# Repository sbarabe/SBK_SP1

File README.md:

# SBK_SP1

<p align="center">
  
  &nbsp;&nbsp;&nbsp;
  
</p>

<p align="center">
  <b>Front</b> &nbsp;&nbsp;&nbsp;&nbsp;&nbsp;&nbsp;&nbsp;&nbsp;&nbsp;&nbsp;&nbsp;&nbsp;&nbsp;&nbsp;&nbsp;&nbsp;&nbsp;&nbsp;&nbsp;&nbsp;&nbsp;&nbsp;&nbsp;&nbsp;&nbsp;&nbsp;&nbsp;
  <b>Back</b>
</p>

---

## Open-source soft power switch module for learning and embedded electronics projects.

**SBK_SP1** is a compact, reusable soft power switch module for battery-powered and low-voltage embedded systems. 

A momentary push button, maintained switch, or external control can turn the system on. Once powered, a microcontroller can assert the **HOLD** input to keep the system running independently of the switch state. 

**Version 2.0** adds an onboard start button, a dedicated external **SW** input, and an independent **SENS** output. This allows the microcontroller to continue monitoring the external switch while holding its own power on, making graceful software-controlled shutdown possible. 

Designed for breadboards, prototypes, and educational projects, **SBK_SP1** provides an easy way to add soft power management to Arduino, ESP32, RP2040, ATtiny, STM32, and similar microcontroller-based systems.

---

## Features

- Input voltage: **2–12 VDC**
- Load current: **up to 2 A**
- High-side **P-channel MOSFET** switching
- MCU-controlled soft power latch
- Onboard power/start button
- External momentary button or maintained switch input
- Independent switch-state sensing
- Supports graceful MCU-controlled shutdown
- Ultra-low off-state current (< 1 µA typ.)
- Power input and output status LEDs
- Breadboard-friendly 2.54 mm pin header
- Open-source hardware
- Optimized for low-cost assembly using JLCPCB Basic components

---

## Specifications 
| Parameter | Specification | 
|---|---| 
| Input voltage | 2–12 VDC | 
| Maximum load | 2 A | 
| Off-state current | < 1 µA typical | 
| HOLD input | Active HIGH, 2 V–VIN | 
| SW input | Active LOW, connect to GND | 
| SENS output | Active LOW, external/MCU pull-up required | 
| PCB size | 15.8 × 11.2 mm | | Pin pitch | 2.54 mm |

---

## Pinout

| Pin | Description |
|------|-------------|
| **VIN** | Power input (2–12 VDC) |
| **GND** | Ground |
| **VOUT** | Switched power output |
| **HOLD** | Active-HIGH MCU power-hold input. Drive HIGH (2 V–VIN) to keep VOUT enabled. | 
| **SW** | Active-LOW external switch input. Connect to GND to start/activate the module. | 
| **SENS** | Active-LOW switch-sense output. Connect to an MCU input with an internal or external pull-up. | 

The onboard push button is connected to the **SW** and **SENS** functions and can be used to start the module without an external switch.

---

## Typical Application

```text
Battery / Power Supply
         │
         │
        VIN
   ┌───────────┐
   │  SBK_SP1  │
   │           │
   │   VOUT    ├──────────> Embedded System Power
   │           │
MCU├─ HOLD <───┤ MCU output
   │           │
MCU├─ SENS ───>│ MCU input with pull-up
   │           │
   │    SW     ├──── Switch / Push Button ──── GND
   └───────────┘
         │
        GND
```

---

## Operation

### Power On
1. The user presses the onboard button or connects **SW** to GND.
2. The hardware immediately enables the high-side power MOSFET.
3. **VOUT** powers the microcontroller and load.
4. **SENS** goes **LOW**, allowing the microcontroller to detect the active switch.
5. The microcontroller boots and drives **HOLD HIGH**.
6. The module remains powered after a momentary button is released.

### Power Hold

While **HOLD** is **HIGH**, the microcontroller keeps **VOUT** enabled independently of the state of **SW**.

Because **SENS** monitors the switch separately from the **HOLD** circuit, the microcontroller can continue detecting button presses, button releases, or changes in a maintained external switch while power remains latched.

### Graceful Shutdown

With a maintained ON/OFF switch, SBK_SP1 can support a software-controlled shutdown sequence:

1. The external switch connects **SW** to **GND** to start the system.
2. The microcontroller boots and drives **HOLD HIGH**.
3. The user opens the external switch.
4. **SENS** returns **HIGH** while **HOLD** keeps the system powered.
5. The microcontroller detects the switch change and performs any required shutdown tasks.
6. When shutdown is complete, the microcontroller drives **HOLD LOW**.
7. **SBK_SP1** disconnects **VOUT** from the load.

This allows firmware to save data, stop peripherals, or perform other cleanup before removing power.

---

## Using a Momentary Push Button

SBK_SP1 can also be used with a conventional momentary push button.

Connect the external button between **SW** and **GND**, or simply use the onboard button.

A button press starts the system and pulls **SENS LOW**. The microcontroller can then assert **HOLD** to keep itself powered after the button is released.

Because **SENS** remains independent of **HOLD**, the same button can continue to be monitored by the firmware while the system is running.

---

## Applications

### Microcontroller platforms

- Arduino
- ESP32
- RP2040
- ATtiny
- STM32

### Example applications

- Portable instruments
- Battery-powered sensors
- Educational electronics projects
- Custom embedded devices
  
---

## Notes

- **HOLD** is an active-HIGH input and should not exceed **VIN**.
- **SW** is an active-LOW input and is activated by connecting it to **GND**.
- **SENS** is an active-LOW sense signal and requires an external or MCU internal pull-up.
- The onboard push button and external **SW** input operate in parallel.
- Do not apply an external positive voltage directly to **SW**.
- Inductive loads require an external flyback diode or equivalent protection.
- High-capacitance loads may require inrush-current limiting.
- The 2 A rating is the maximum recommended module load; consider wiring, connector, thermal, and application conditions when operating near the maximum current.

---

## Getting Started

This project is fully open-source hardware. You can:

- Build your own module using the provided KiCad design files.
- Modify the design to suit your application.
- Manufacture your own boards.

### Assembled Modules

If you prefer a ready-to-use module, fully assembled SBK_SP1 boards may be available in small batches on demand.

For availability, pricing, or quantity inquiries, contact:

📧 **SmartBuildsKits@gmail.com**

These modules are intended for hobbyists, educators, prototypes, and small-scale projects. Availability depends on component stock and production capacity.

---

## Related Projects

- [**SBK_FET1**](https://github.com/sbarabe/SBK_FET1) – N-Channel/P-Channel FET modules
- [**SBK_RP1**](https://github.com/sbarabe/SBK_RP1) – Reverse Polarity Protection Module
- [**MémoBot**](https://github.com/sbarabe/MemoBot) – Educational memory game built using SBK_SP1 and SBK_RP1

---

## Contributing

Suggestions, bug reports, and improvements are welcome.

To report a problem or suggest an improvement, open an Issue. Pull Requests are also welcome for corrections, documentation improvements, and design changes that make the project easier to understand or build.

---

## Support the Project

If this project is useful for learning, teaching, or prototyping, you can support its continued development.

Donations help fund prototype hardware, documentation, educational resources, and future open-source projects.

❤️ [**Support the project through PayPal**](https://paypal.me/sbarab?country.x=CA&locale.x=fr_CA)

Thank you for supporting open-source educational hardware.

---

## License

This project is released as open-source hardware under the **CERN Open Hardware Licence Version 2 - Permissive (CERN-OHL-P v2)**.

You are free to study, modify, manufacture, and distribute this design, provided the terms of the license are respected.

See the [LICENSE](LICENSE) file for the full license text.

---

## Design Files

This project was designed using **KiCad 10**.

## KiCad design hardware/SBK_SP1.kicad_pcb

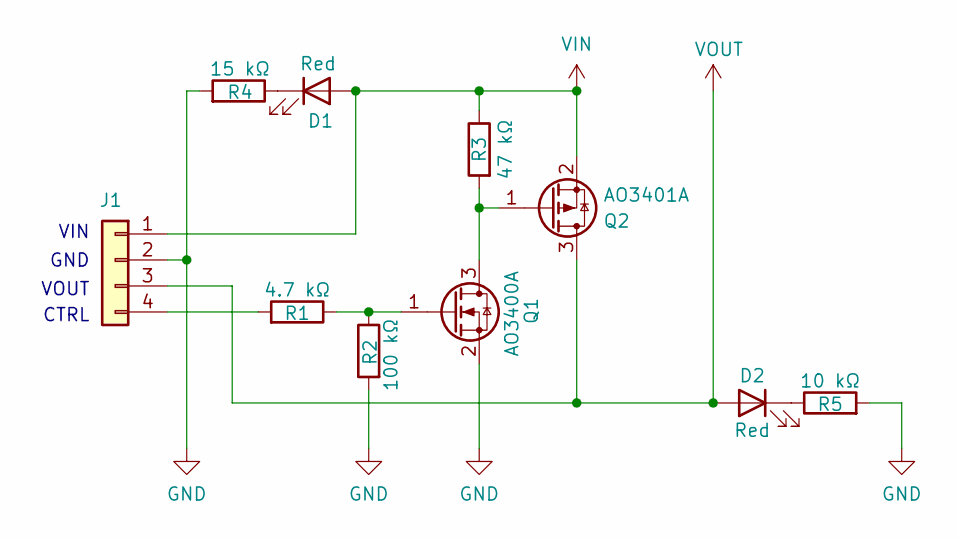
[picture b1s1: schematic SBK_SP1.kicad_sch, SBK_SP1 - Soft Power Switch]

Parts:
D1, D2: Red; LED_0603_1608Metric
J1: 1x4 pin header; PinHeader_1x04_P2.54mm_Vertical
Q1: AO3400A; SOT-23
Q2: AO3401A; SOT-23
R1: 4.7 kΩ; R_0402_1005Metric
R2: 100 kΩ; R_0603_1608Metric
R3: 47 kΩ; R_0402_1005Metric
R4: 15 kΩ; R_0402_1005Metric
R5: 10 kΩ; R_0402_1005Metric

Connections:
GND: J1.2, Q1.2 (S), R2.2, R4.2, R5.2
unnamed: D1.1 (K), R4.1
unnamed: D2.1 (K), R5.1
unnamed: J1.4, R1.2
unnamed: Q1.3 (D), Q2.1 (G), R3.2
unnamed: Q1.1 (G), R1.1, R2.1
VIN: D1.2 (A), J1.1, Q2.2 (S), R3.1
VOUT: D2.2 (A), J1.3, Q2.3 (D)

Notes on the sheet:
VOUT
VIN
CTRL
GND

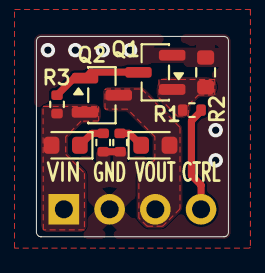
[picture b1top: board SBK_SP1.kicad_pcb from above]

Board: 2 copper layers, 10.7 x 11.1 mm, 10 parts (1 on the bottom side), 8 nets.

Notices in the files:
hardware/SBK_SP1.kicad_sch:
Licensed under CERN-OHL-P-2.0
